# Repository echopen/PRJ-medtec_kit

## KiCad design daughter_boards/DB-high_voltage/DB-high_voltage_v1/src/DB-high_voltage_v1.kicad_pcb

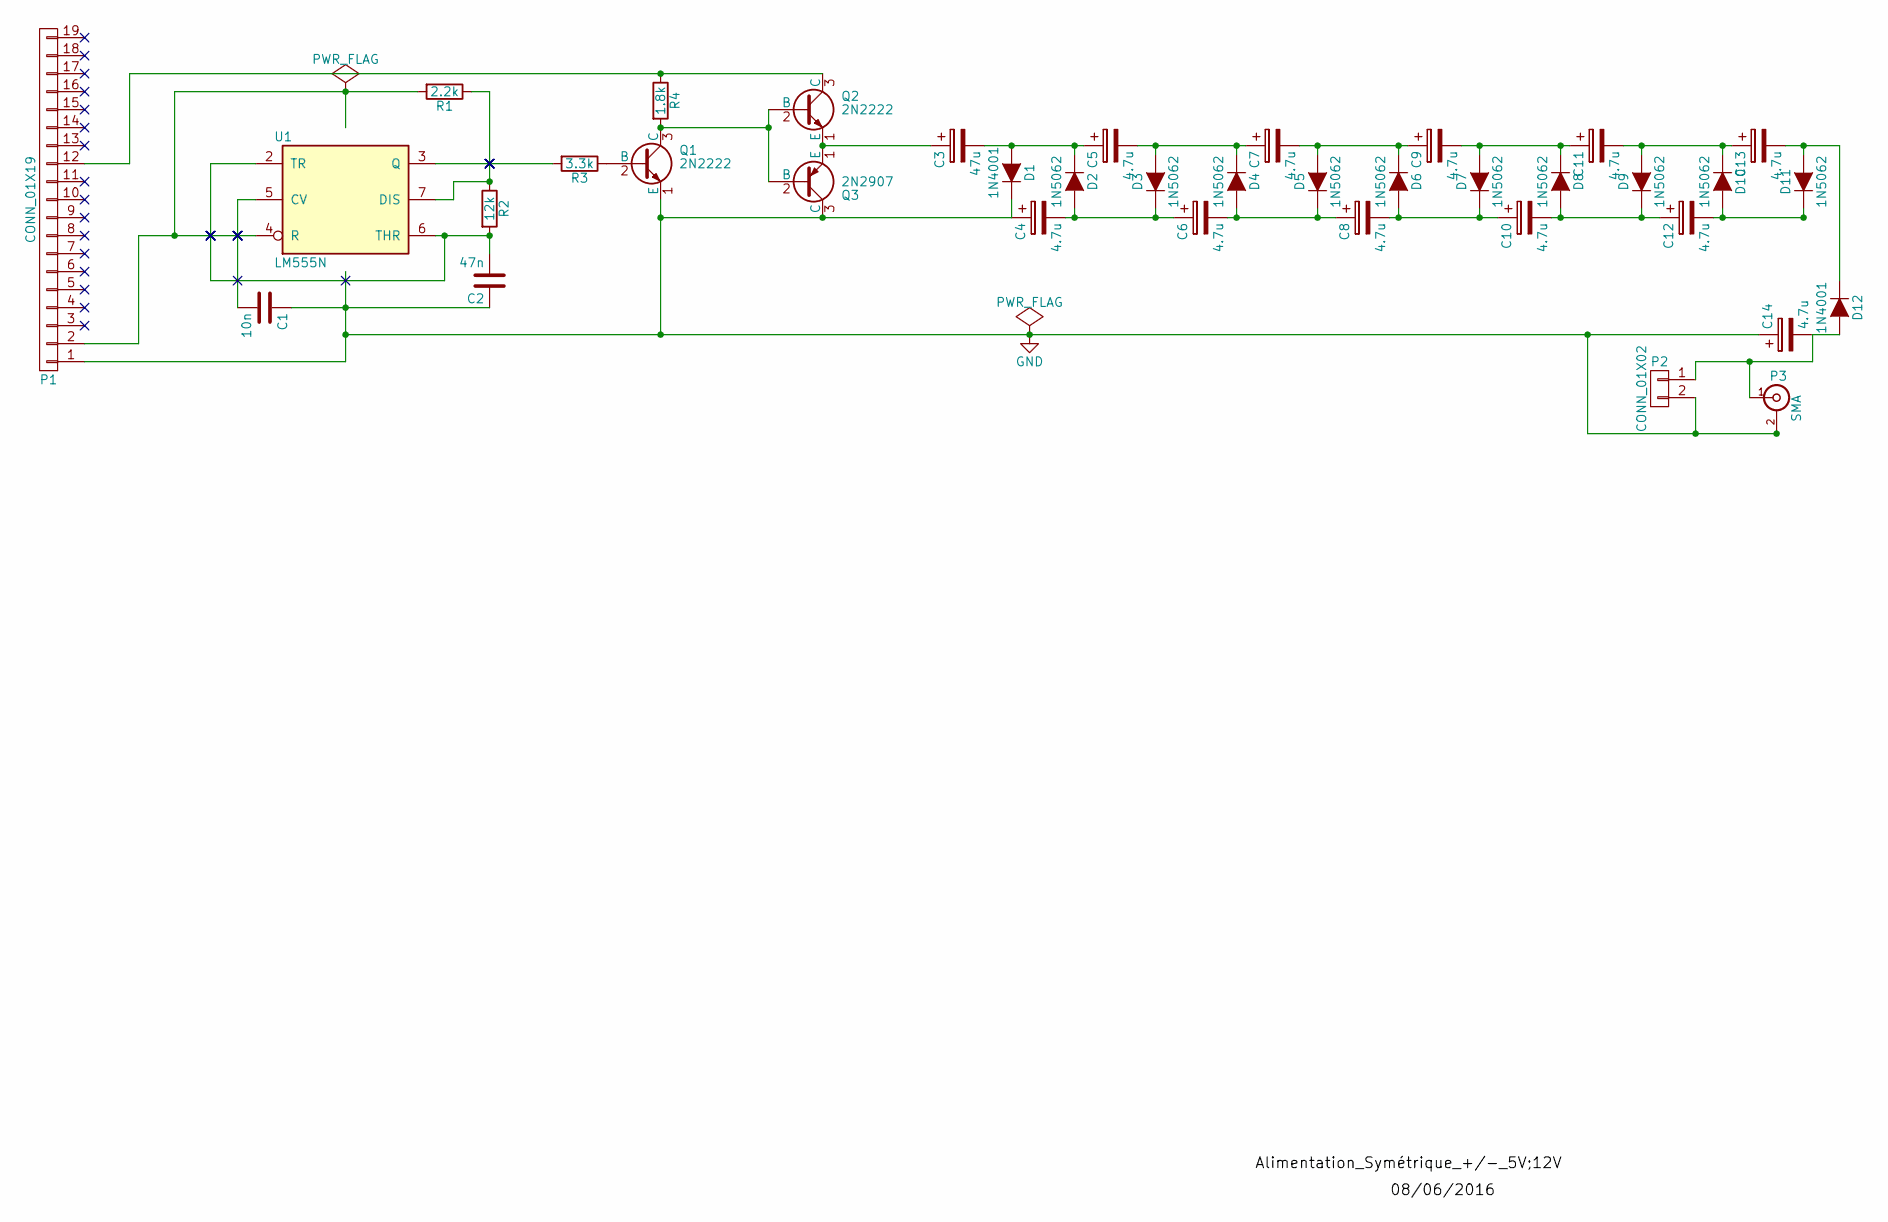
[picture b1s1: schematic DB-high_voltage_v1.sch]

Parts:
C1: 10n; C_Radial_D5_L6_P2.5
C2: 47n; C_Radial_D5_L6_P2.5
C3: 47u; C_Radial_D5_L6_P2.5
C4, C5, C6, C7, C8, C9, C10, C11, C12, C13, C14: 4.7u; C_Radial_D5_L6_P2.5
D1, D12: 1N4001; Diode_DO-35_SOD27_Horizontal_RM10
D2, D3, D4, D5, D6, D7, D8, D9, D10, D11: 1N5062; Diode_DO-35_SOD27_Horizontal_RM10
P1: CONN_01X19; Header_pin_angled_1x19
P2: CONN_01X02; Socket_Strip_Straight_1x02
P3: SMA
Q1, Q2: 2N2222; TO-18_3Pin
Q3: 2N2907; TO-18_3Pin
R1: 2.2k; Resistor_Horizontal_RM10mm
R2: 12k; Resistor_Horizontal_RM10mm
R3: 3.3k; Resistor_Horizontal_RM10mm
R4: 1.8k; Resistor_Horizontal_RM10mm
U1: LM555N; DIP-8_W7.62mm

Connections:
GND: C1.1, C2.1, C4.1, C14.1, D1.1 (K), P1.1, P2.2, P3.2 (Ext), Q1.1 (E), Q3.3 (C), U1.1 (GND)
unnamed: C1.2, U1.5 (CV)
unnamed: C2.2, R2.2, U1.2 (TR), U1.6 (THR)
unnamed: C3.1, Q2.1 (E), Q3.1 (E)
unnamed: C3.2, C5.1, D1.2 (A), D2.1 (K)
unnamed: C4.2, C6.1, D2.2 (A), D3.1 (K)
unnamed: C5.2, C7.1, D3.2 (A), D4.1 (K)
unnamed: C6.2, C8.1, D4.2 (A), D5.1 (K)
unnamed: C7.2, C9.1, D5.2 (A), D6.1 (K)
unnamed: C8.2, C10.1, D6.2 (A), D7.1 (K)
unnamed: C10.2, C12.1, D8.2 (A), D9.1 (K)
unnamed: C9.2, C11.1, D7.2 (A), D8.1 (K)
unnamed: C11.2, C13.1, D9.2 (A), D10.1 (K)
unnamed: C12.2, D10.2 (A), D11.1 (K)
unnamed: C13.2, D11.2 (A), D12.1 (K)
unnamed: C14.2, D12.2 (A), P2.1, P3.1 (In)
unnamed: P1.12, Q2.3 (C), R4.1
unnamed: Q1.2 (B), R3.1
unnamed: Q1.3 (C), Q2.2 (B), Q3.2 (B), R4.2
unnamed: R1.1, R2.1, U1.7 (DIS)
unnamed: R3.2, U1.3 (Q)
VCC: P1.2, R1.2, U1.4 (R), U1.8 (VCC)

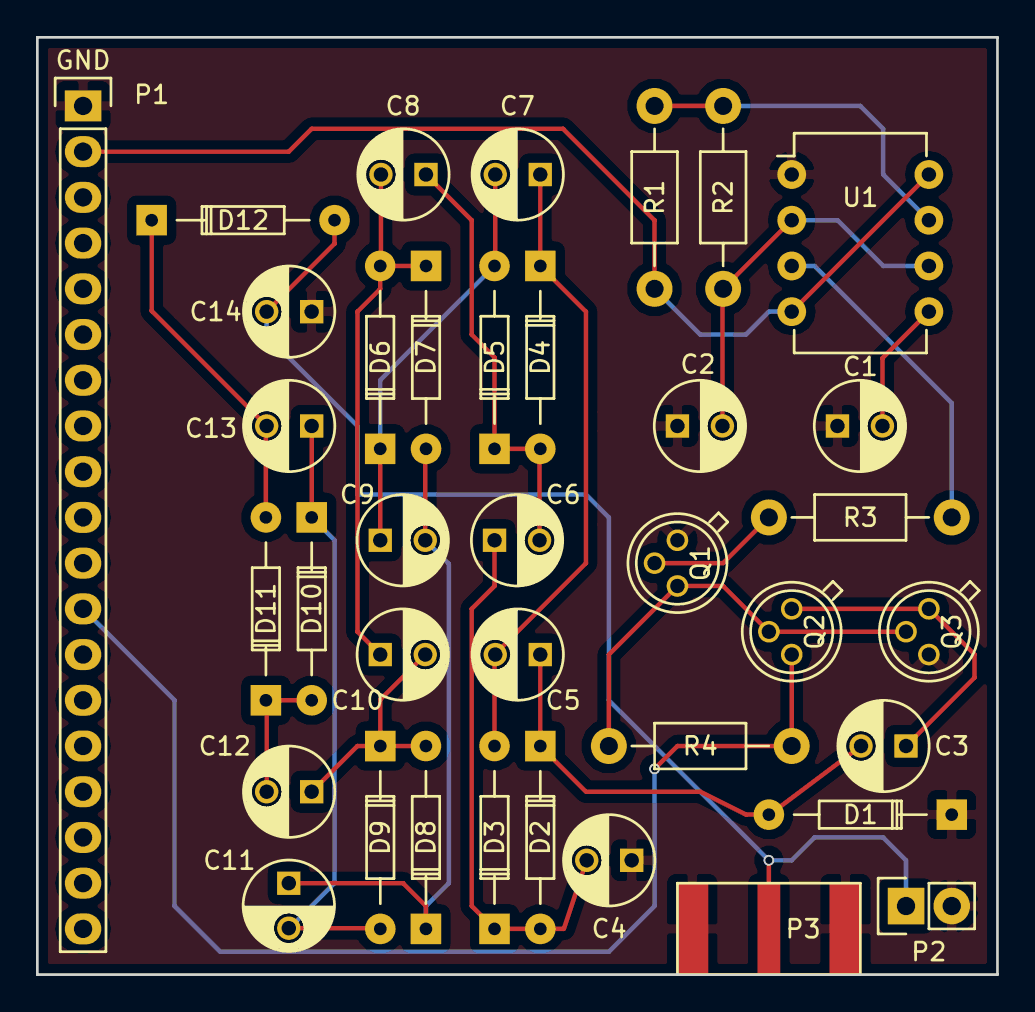
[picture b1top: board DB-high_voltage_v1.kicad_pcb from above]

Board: 2 copper layers, 53.3 x 52.1 mm, 37 parts (0 on the bottom side), 22 nets.

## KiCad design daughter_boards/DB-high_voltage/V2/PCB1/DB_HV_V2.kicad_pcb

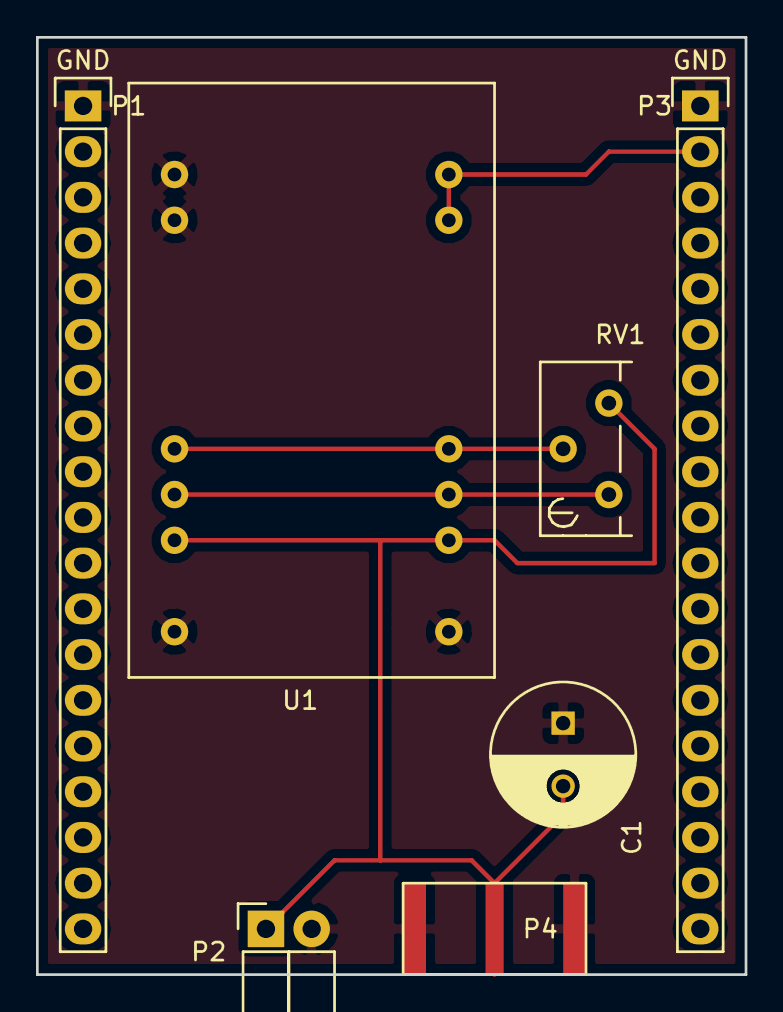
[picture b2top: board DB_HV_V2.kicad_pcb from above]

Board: 2 copper layers, 39.4 x 52.1 mm, 7 parts (0 on the bottom side), 5 nets.

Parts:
C1: 4,7u (150V); CP_TH_common
P1, P3: CONN_01X19; Header_pin_1x19
P2: CONN_01X02; Socket_Strip_Angled_1x02
P4: SMA
RV1: POT; Potentiometer_Bourns_3296Y_3-8Zoll_Angular_ScrewUp
U1: R05-100B; RECOM

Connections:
GND: C1.1, P1.1, P2.2, P3.1, P4.2, U1.2, U1.3, U1.12, U1.13
unnamed: C1.2, P2.1, P4.1, RV1.3, U1.10, U1.15
unnamed: P3.2, U1.22, U1.23
unnamed: RV1.1, U1.9, U1.16
unnamed: RV1.2, U1.8, U1.17

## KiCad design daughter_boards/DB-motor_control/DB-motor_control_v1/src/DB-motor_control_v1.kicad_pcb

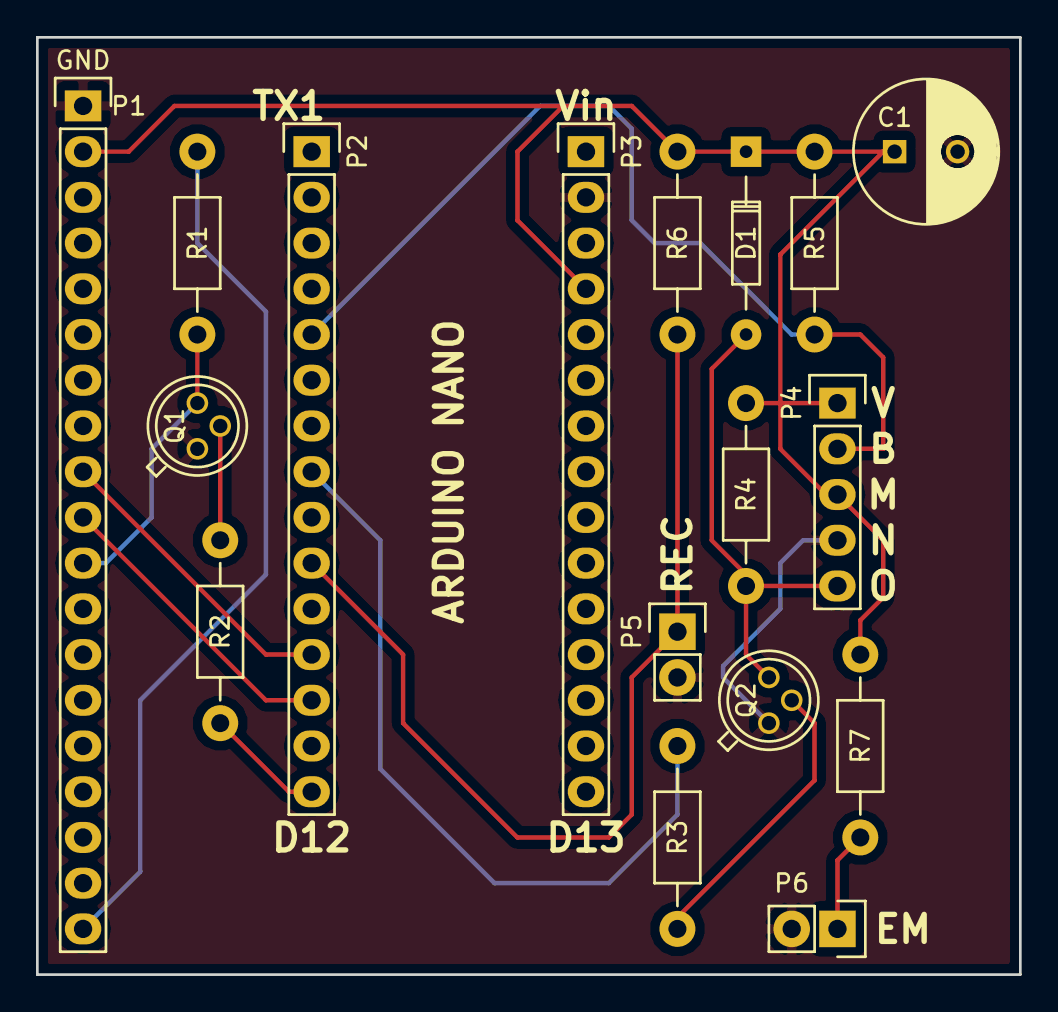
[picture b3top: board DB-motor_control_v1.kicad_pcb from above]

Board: 2 copper layers, 54.6 x 52.1 mm, 17 parts (0 on the bottom side), 14 nets.

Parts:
C1: 10u; CP_TH_common
D1: 1N4001; D_TH_common
P1: CONN_01X19; Header_pin_angled_1x19
P2, P3: CONN_01X15; Socket_Strip_Straight_1x15
P4: CONN_01X05; Socket_Strip_Straight_1x05
P5, P6: CONN_01X02; Socket_Strip_Straight_1x02
Q1, Q2: 2N2222; TO-18_TH_common
R1, R2: 1.5k; Resistor_TH_common
R3: 680; Resistor_TH_common
R4: 1k; Resistor_TH_common
R5: 33k; Resistor_TH_common
R6: 2.2k; Resistor_TH_common
R7: 330; Resistor_TH_common

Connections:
GND: C1.2, P1.1, P3.2, P4.4, P5.2, P6.2, Q1.1, Q2.1
unnamed: C1.1, D1.1, P1.2, P3.4, P4.1, P4.3, R4.1, R5.2, R6.1, R7.1
unnamed: D1.2, P4.5, Q2.3, R4.2
unnamed: P1.9, P2.12
unnamed: P1.10, P2.13
unnamed: P1.11, Q1.3, R1.2
unnamed: P1.19, R1.1
unnamed: P2.5, P4.2, R5.1
unnamed: P2.8, R3.2
unnamed: P2.10, P5.1, R6.2
unnamed: P2.15, R2.1
unnamed: P6.1, R7.2
unnamed: Q1.2, R2.2
unnamed: Q2.2, R3.1

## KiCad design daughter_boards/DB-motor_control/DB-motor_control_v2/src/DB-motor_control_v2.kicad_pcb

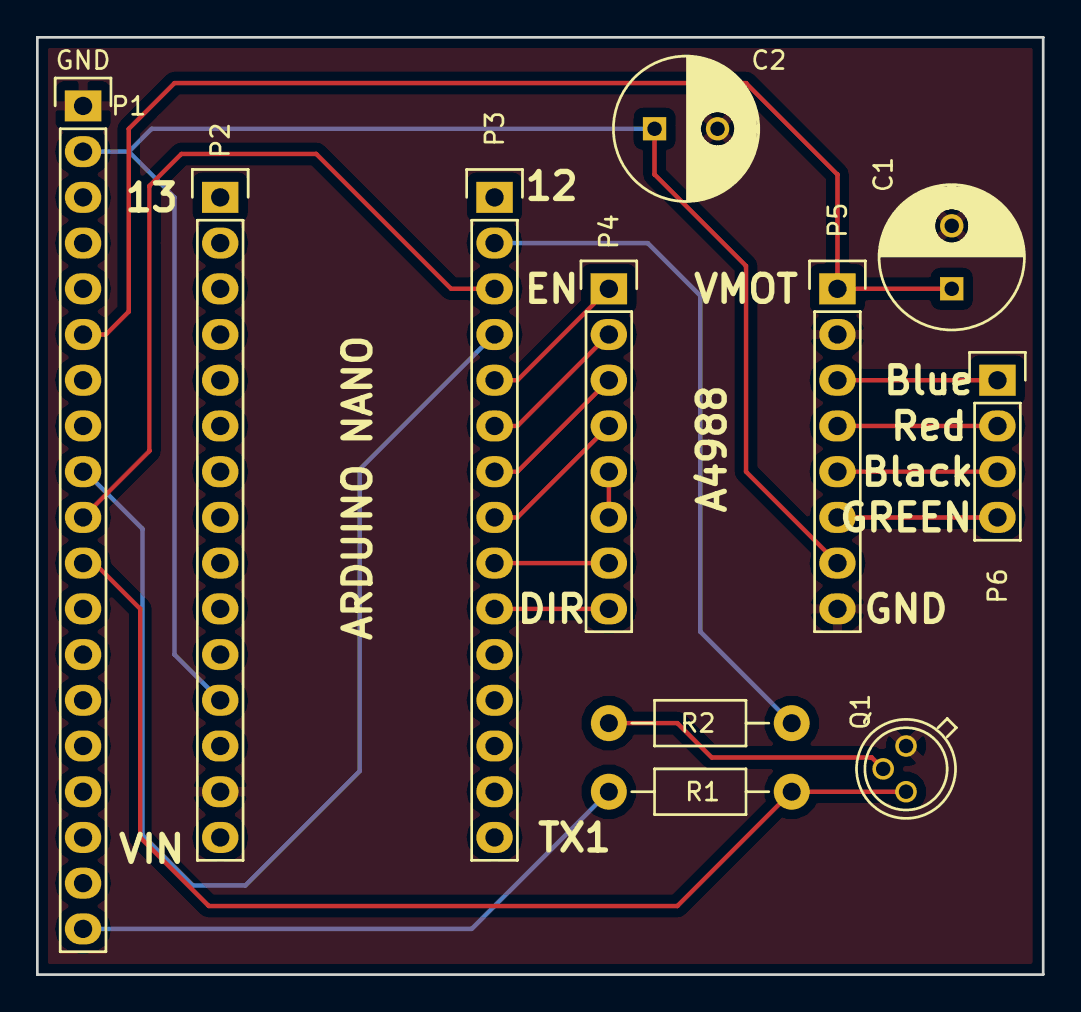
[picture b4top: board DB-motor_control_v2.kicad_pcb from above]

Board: 2 copper layers, 55.9 x 52.1 mm, 11 parts (0 on the bottom side), 20 nets.

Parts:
C1: 100u; CP_TH_common
C2: 10u; CP_TH_common
P1: CONN_01X19; Header_pin_angled_1x19
P2, P3: CONN_01X15; Socket_Strip_Straight_1x15
P4, P5: CONN_01X08; Socket_Strip_Straight_1x08
P6: CONN_01X04; Socket_Strip_Straight_1x04
Q1: 2N2222; TO-18_TH_common
R1, R2: 1.5k; Resistor_TH_common

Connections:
GND: C1.2, C2.2, P1.1, P2.14, P5.2, P5.8, Q1.1
unnamed: C1.1, P1.6, P5.1
unnamed: C2.1, P1.2, P2.12, P5.7
unnamed: P1.9, P3.4
unnamed: P1.10, P3.3
unnamed: P1.11, Q1.3, R1.2
unnamed: P1.19, R1.1
unnamed: P3.2, R2.2
unnamed: P3.5, P4.1
unnamed: P3.6, P4.2
unnamed: P3.7, P4.3
unnamed: P3.8, P4.4
unnamed: P3.9, P4.7
unnamed: P3.10, P4.8
unnamed: P4.5, P4.6
unnamed: P5.3, P6.1
unnamed: P5.4, P6.2
unnamed: P5.5, P6.3
unnamed: P5.6, P6.4
unnamed: Q1.2, R2.1
